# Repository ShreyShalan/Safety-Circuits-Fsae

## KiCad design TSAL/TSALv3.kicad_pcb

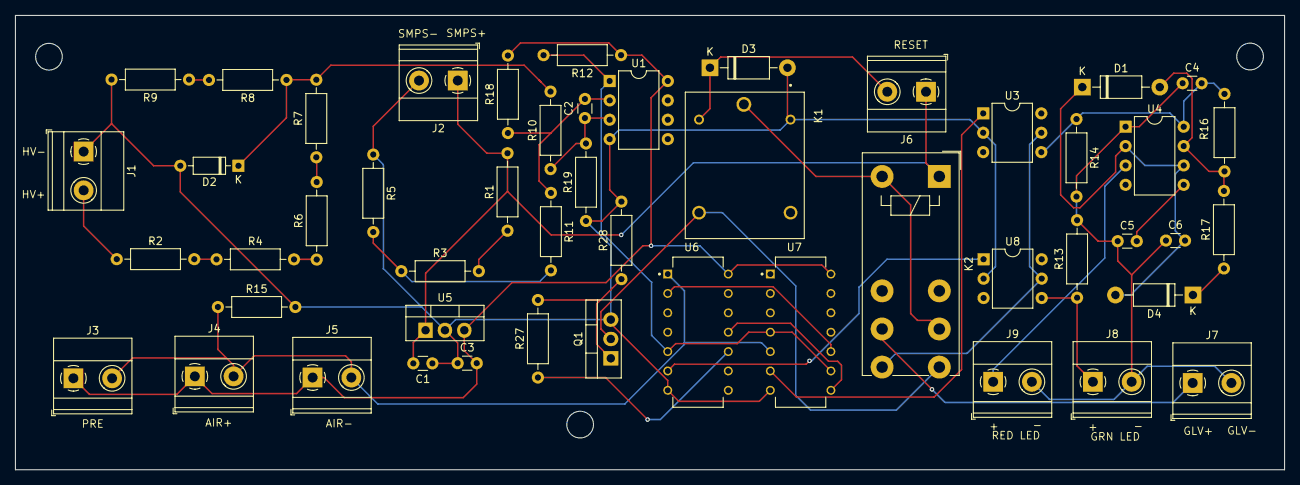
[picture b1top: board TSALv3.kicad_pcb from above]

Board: 2 copper layers, 166.4 x 59.6 mm, 50 parts (0 on the bottom side), 34 nets.

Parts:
C1: 0.33u; C_Disc_D3.0mm_W1.6mm_P2.50mm
C2: 10n; C_Disc_D3.0mm_W1.6mm_P2.50mm
C3: 0.1u; C_Disc_D3.0mm_W1.6mm_P2.50mm
C4, C5: 100n; C_Disc_D3.0mm_W1.6mm_P2.50mm
C6: 1u; C_Disc_D3.0mm_W1.6mm_P2.50mm
D1, D3, D4: 1N4002; D_DO-41_SOD81_P10.16mm_Horizontal
D2: 12V; D_DO-35_SOD27_P7.62mm_Horizontal
J1, J2, J3, J4, J5, J6, J7, J8, J9: Screw_Terminal_01x02; TerminalBlock_Phoenix_MKDS-1,5-2-5.08_1x02_P5.08mm_Horizont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
K1: SRD-12VDC-SL-C; RELAY_SRD-12VDC-SL-C
K2: FINDER-40.52; Relay_DPDT_Finder_40.52
Q1: IRF540N; TO-220-3_Vertical
R1, R13, R14, R15, R28: 10k; R_Axial_DIN0207_L6.3mm_D2.5mm_P10.16mm_Horizontal
R2, R4, R6: 47k; R_Axial_DIN0207_L6.3mm_D2.5mm_P10.16mm_Horizontal
R3, R8, R9, R12, R18, R19: 1k; R_Axial_DIN0207_L6.3mm_D2.5mm_P10.16mm_Horizontal
R5: 1K; R_Axial_DIN0207_L6.3mm_D2.5mm_P10.16mm_Horizontal
R7: 249k; R_Axial_DIN0207_L6.3mm_D2.5mm_P10.16mm_Horizontal
R10, R11, R27: 100; R_Axial_DIN0207_L6.3mm_D2.5mm_P10.16mm_Horizontal
R16, R17: 180k; R_Axial_DIN0207_L6.3mm_D2.5mm_P10.16mm_Horizontal
U1: LM393; DIP-8_W7.62mm
U3, U8: 4N35; DIP-6_W7.62mm
U4: NE555P; DIP-8_W7.62mm
U5: L7805; TO-220-3_Vertical
U6: SN74LS04N; DIP794W45P254L1969H508Q14
U7: SN74LS08N; DIP794W45P254L1969H508Q14

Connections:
+5V: C3.2, J3.1, J4.1, J5.1, R12.1, R18.2, U1.8 (V+), U5.3 (OUT), U6.14 (VCC), U7.14 (VCC)
+12V: C1.2, J2.1, J6.1, K2.A1, R1.2, U5.1 (IN)
/+HV: J1.2, R2.1
/GRN+: J8.1, R13.1, U8.4
/RED+: J9.1, U4.3 (Q)
/Vin: D2.1 (K), R7.2, R8.1, R10.2
/Vref: R3.1, R5.2, R11.2
AIR State: J3.2, J4.2, J5.2, R15.1, U6.1 (1A), U7.5 (2B)
AUX Open: U6.2 (1Y), U7.10 (3B)
GLV supply: K2.24, U3.5, U8.5
GLV+: J7.1, K2.21
GLV-: C4.1, C5.1, C6.1, J7.2, J8.2, J9.2, R13.2, R14.2, U4.1 (GND)
GND: C1.1, C3.1, D2.2 (A), D3.2 (A), J1.1, J2.2, K1.COIL1, Q1.3 (S), R5.1, R9.2, R15.2, R19.1, R28.2, U1.4 (V-), U3.2, U5.2 (GND), U6.7 (GND), U7.7 (GND), U8.2
unnamed: D1.2 (A), R16.1, R17.2, U4.7 (DIS)
unnamed: C6.2, D1.1 (K), D4.2 (A), U4.2 (TR), U4.6 (THR)
unnamed: D4.1 (K), R17.1
unnamed: K1.COM, K2.11, K2.A2
unnamed: K1.NO, K2.14, Q1.2 (D)
unnamed: Q1.1 (G), R27.2, R28.1
unnamed: R1.1, R3.2
unnamed: R2.2, R4.1
unnamed: R4.2, R6.1
unnamed: R6.2, R7.1
unnamed: R8.2, R9.1
unnamed: C2.1, R10.1, R19.2, U1.3 (+)
unnamed: C2.2, R11.1, R18.1, U1.2 (-)
unnamed: C5.2, U4.5 (CV)
unnamed: C4.2, R14.1, R16.2, U3.4, U4.8 (VCC)
RED ON: U3.1, U7.6 (2Y)
TS Status: R12.2, U1.1, U6.5 (3A), U7.4 (2A), U7.9 (3A)
TS' Status: U6.6 (3Y), U8.1
TSAL Error: U6.11 (5A), U7.8 (3Y)
TSAL Error': R27.1, U6.10 (5Y)
reset: D3.1 (K), J6.2, K1.COIL2

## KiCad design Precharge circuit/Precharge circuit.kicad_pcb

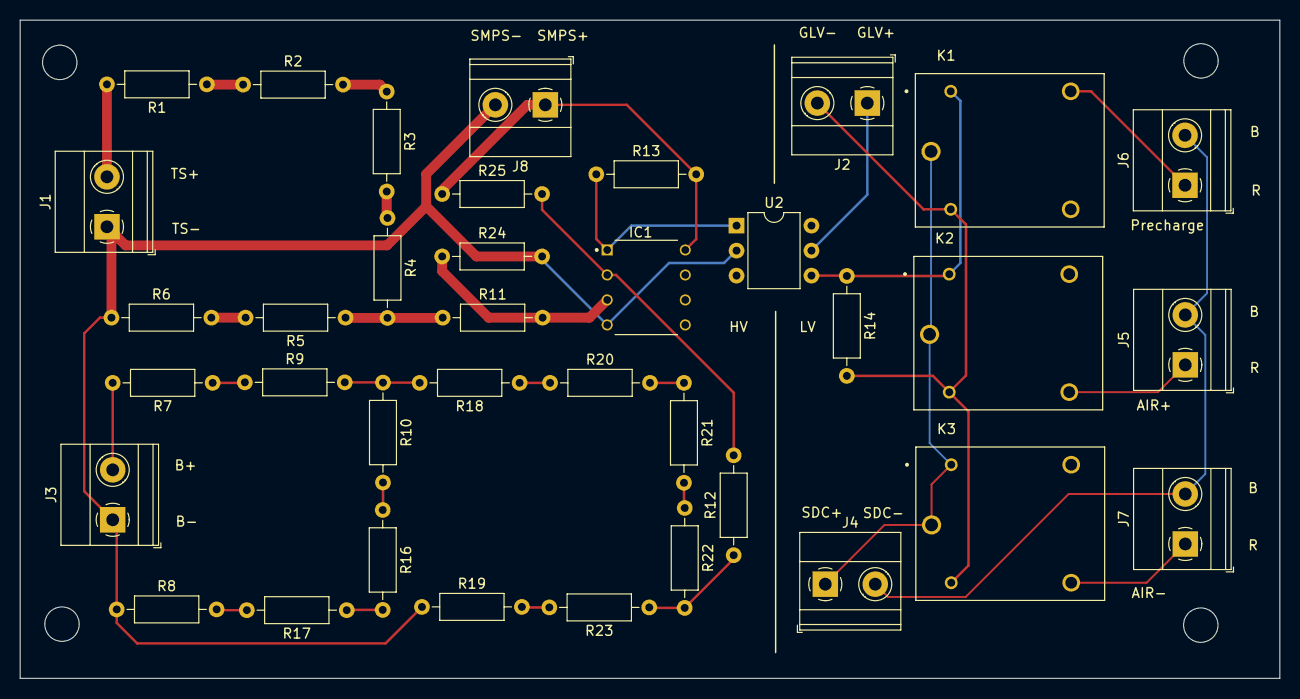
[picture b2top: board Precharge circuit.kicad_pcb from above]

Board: 2 copper layers, 128.1 x 66.9 mm, 37 parts (0 on the bottom side), 30 nets.

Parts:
IC1: LM393AN; DIP794W45P254L959H508Q8
J1, J3: Conn_01x02_Socket; TerminalBlock_Phoenix_MKDS-1,5-2-5.08_1x02_P5.08mm_Horizont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
J2, J4, J5, J6, J7, J8: Screw_Terminal_01x02; TerminalBlock_Phoenix_MKDS-1,5-2-5.08_1x02_P5.08mm_Horizont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
K1, K2, K3: SRD-12VDC-SL-C; RELAY_SRD-12VDC-SL-C
R1, R2, R10, R16, R18, R20: 120k; R_Axial_DIN0207_L6.3mm_D2.5mm_P10.16mm_Horizontal
R3, R17, R21: 82k; R_Axial_DIN0207_L6.3mm_D2.5mm_P10.16mm_Horizontal
R4, R5, R6, R19, R22, R23: 1k; R_Axial_DIN0207_L6.3mm_D2.5mm_P10.16mm_Horizontal
R7, R9, R13, R14, R24, R25: 10k; R_Axial_DIN0207_L6.3mm_D2.5mm_P10.16mm_Horizontal
R8: 64k; R_Axial_DIN0207_L6.3mm_D2.5mm_P10.16mm_Horizontal
R11, R12: 100; R_Axial_DIN0207_L6.3mm_D2.5mm_P10.16mm_Horizontal
U2: 4N35; DIP-6_W7.62mm

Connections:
+12V: IC1.8 (VCC), J8.1, R13.2, R25.1
AIR+: J5.1, K2.NO
AIR-: J7.1, K3.NO
GND: IC1.4 (GND), J1.1, J3.1, J8.2, R6.1, R8.1, R19.1, R24.2, U2.2
GND1: J2.2, K1.COIL2, K2.COIL2, K3.COIL2, R14.2
unnamed: IC1.3 (1IN+), R11.2, R24.1
unnamed: IC1.2 (1IN-), R12.2, R25.2
unnamed: IC1.1 (1OUT), R13.1, U2.1
unnamed: J1.2, R1.2
unnamed: J3.2, R7.2
unnamed: R1.1, R2.1
unnamed: R2.2, R3.1
unnamed: R3.2, R4.1
unnamed: R5.2, R6.2
unnamed: R7.1, R9.1
unnamed: R9.2, R10.1, R18.2
unnamed: R10.2, R16.1
unnamed: R4.2, R5.1, R11.1
unnamed: R12.1, R22.2, R23.1
unnamed: R16.2, R17.1
unnamed: R8.2, R17.2
unnamed: R18.1, R20.1
unnamed: R19.2, R23.2
unnamed: R20.2, R21.1
unnamed: R21.2, R22.1
SDC+: J4.1, K1.COM, K2.COM, K3.COIL1, K3.COM
SDC-: J4.2, J5.2, J6.2, J7.2
VCC: J2.1, U2.5
precharge: J6.1, K1.NC
rpower: K1.COIL1, K2.COIL1, R14.1, U2.4

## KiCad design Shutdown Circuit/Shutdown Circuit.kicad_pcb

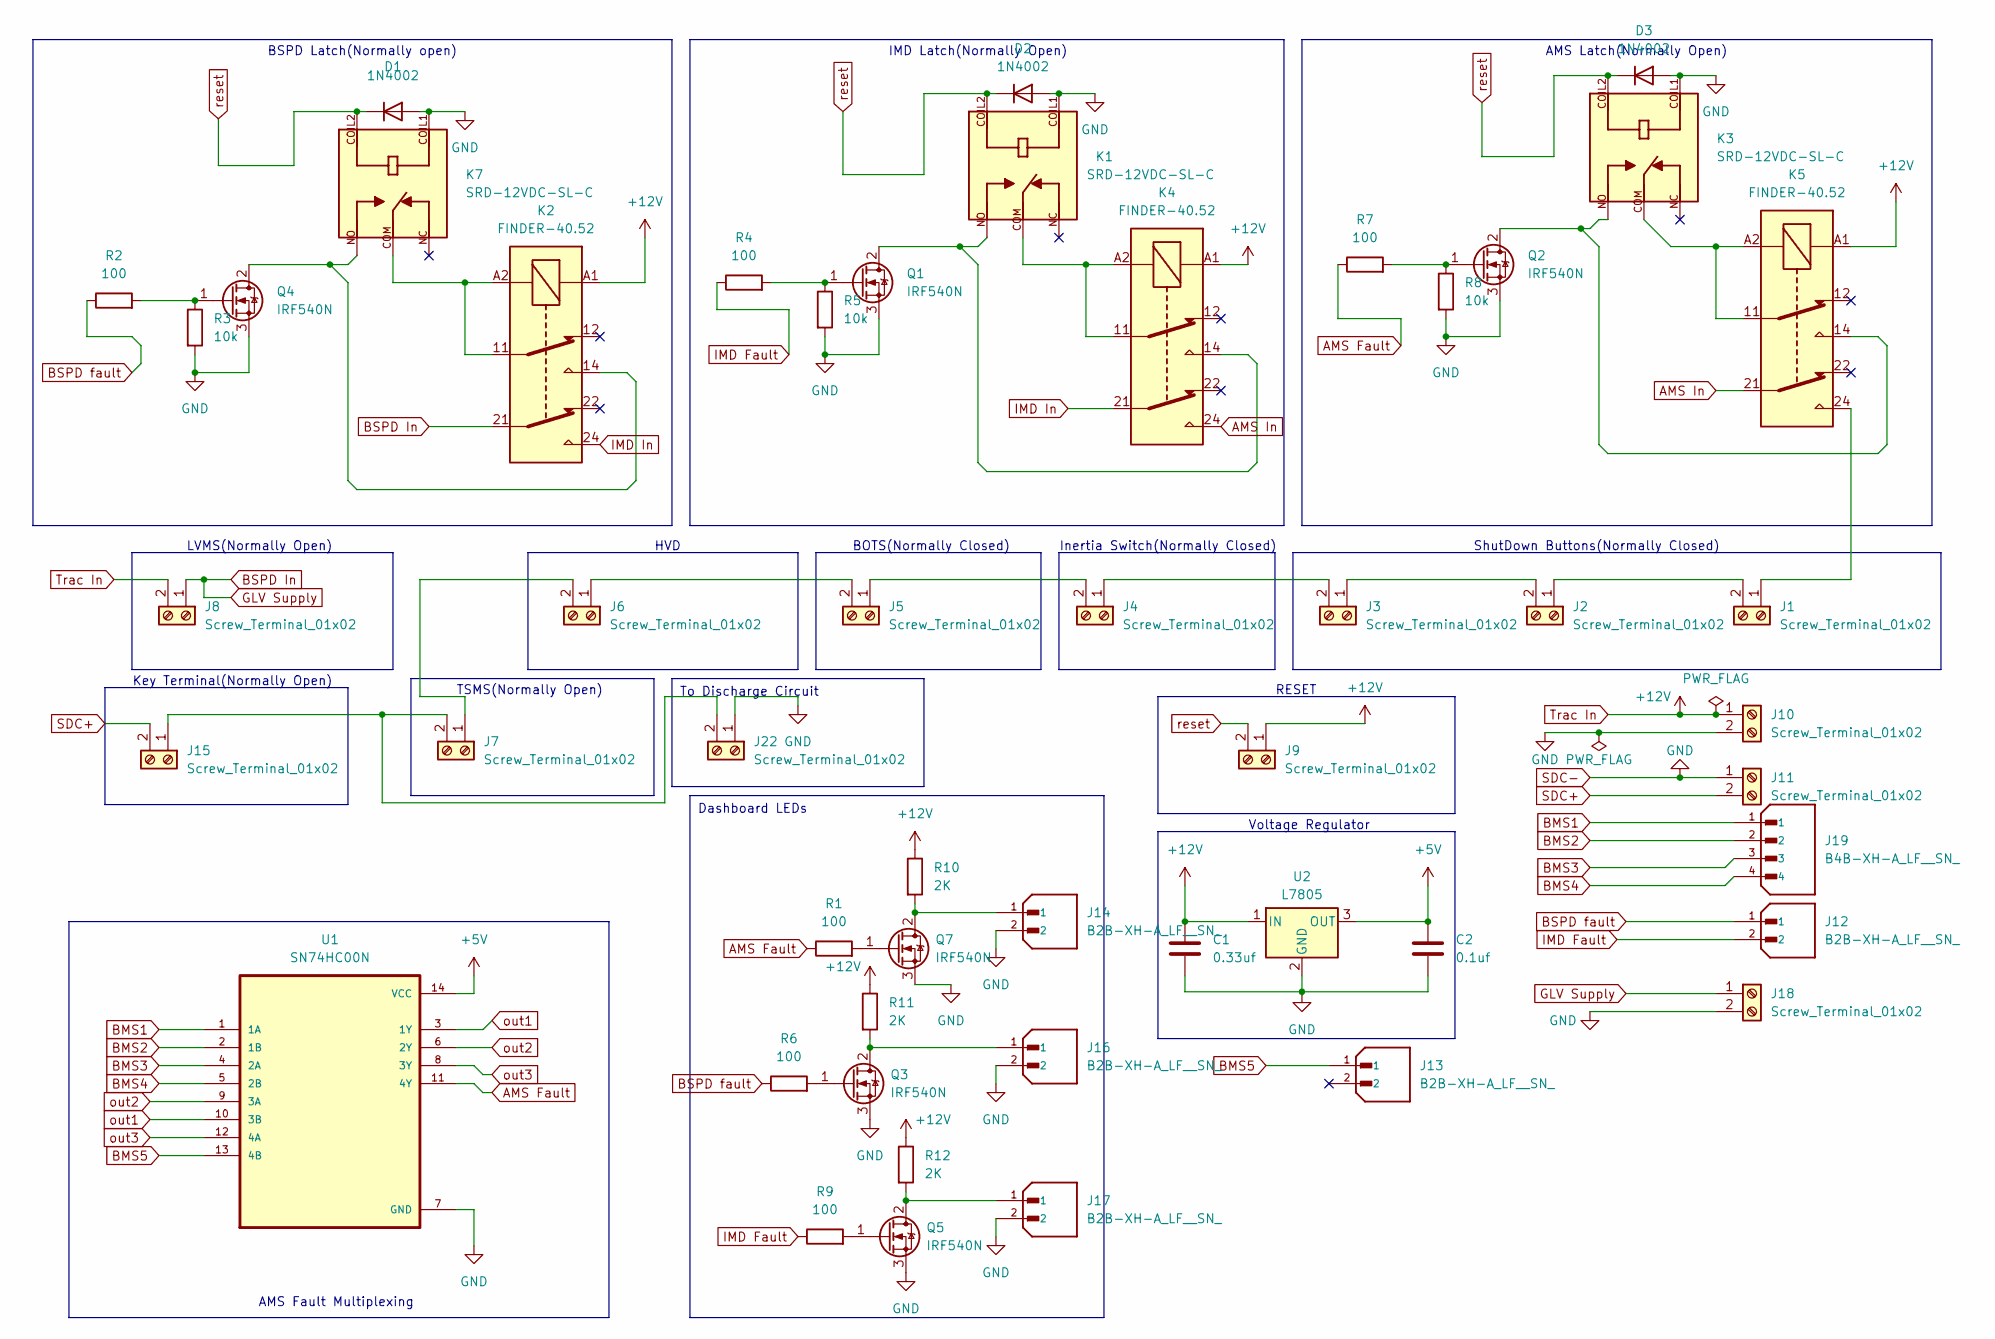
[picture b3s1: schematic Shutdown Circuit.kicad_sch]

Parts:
C1: 0.33uf; C_Disc_D5.0mm_W2.5mm_P5.00mm
C2: 0.1uf; C_Disc_D5.0mm_W2.5mm_P5.00mm
D1, D2, D3: 1N4002; D_DO-41_SOD81_P10.16mm_Horizontal
J1, J2, J3, J4, J5, J6, J7, J8, J9, J10, J11, J15, J18, J22: Screw_Terminal_01x02; TerminalBlock_Phoenix_MKDS-1,5-2-5.08_1x02_P5.08mm_Horizont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
J12, J13, J14, J16, J17: B2B-XH-A_LF__SN_; JST_B2B-XH-A_LF__SN_; PARTREV N/A
J19: B4B-XH-A_LF__SN_; JST_B4B-XH-A_LF__SN_; PARTREV 7/4/21
K1, K3, K7: SRD-12VDC-SL-C; RELAY_SRD-12VDC-SL-C; PARTREV 1.0
K2, K4, K5: FINDER-40.52; Relay_DPDT_Finder_40.52
Q1, Q2, Q3, Q4, Q5, Q7: IRF540N; TO-220-3_Vertical
R1, R2, R4, R6, R7, R9: 100; R_Axial_DIN0207_L6.3mm_D2.5mm_P10.16mm_Horizontal
R3, R5, R8: 10k; R_Axial_DIN0207_L6.3mm_D2.5mm_P10.16mm_Horizontal
R10, R11, R12: 2K; R_Axial_DIN0207_L6.3mm_D2.5mm_P10.16mm_Horizontal
U1: SN74HC00N; DIP794W45P254L1969H508Q14
U2: L7805; TO-220-3_Vertical

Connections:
+5V: C2.1, U1.14 (VCC), U2.3 (OUT)
AMS Fault: R1.1, R7.1, U1.11 (4Y)
AMS In: K4.24, K5.21
BMS1: J19.1, U1.1 (1A)
BMS2: J19.2, U1.2 (1B)
BMS3: J19.3, U1.4 (2A)
BMS4: J19.4, U1.5 (2B)
BMS5: J13.1, U1.13 (4B)
BSPD In: J8.1, J18.1, K2.21
BSPD fault: J12.1, R2.1, R6.1
IMD Fault: J12.2, R4.1, R9.1
IMD In: K2.24, K4.21
unnamed: J1.1, K5.24
unnamed: J1.2, J2.1
unnamed: J2.2, J3.1
unnamed: J3.2, J4.1
unnamed: J4.2, J5.1
unnamed: J5.2, J6.1
unnamed: J6.2, J7.1
unnamed: J7.2, J15.1, J22.2
unnamed: K1.COM, K4.11, K4.A2
unnamed: K2.11, K2.A2, K7.COM
unnamed: K3.COM, K5.11, K5.A2
unnamed: K1.NO, K4.14, Q1.2 (D)
unnamed: Q1.1 (G), R4.2, R5.1
unnamed: K3.NO, K5.14, Q2.2 (D)
unnamed: Q2.1 (G), R7.2, R8.1
unnamed: J16.1, Q3.2 (D), R11.2
unnamed: Q3.1 (G), R6.2
unnamed: K2.14, K7.NO, Q4.2 (D)
unnamed: Q4.1 (G), R2.2, R3.1
unnamed: J17.1, Q5.2 (D), R12.2
unnamed: Q5.1 (G), R9.2
unnamed: J14.1, Q7.2 (D), R10.2
unnamed: Q7.1 (G), R1.2
SDC+: J11.2, J15.2
SDC-: C1.2, C2.2, D1.2 (A), D2.2 (A), D3.2 (A), J10.2, J11.1, J14.2, J16.2, J17.2, J18.2, J22.1, K1.COIL1, K3.COIL1, K7.COIL1, Q1.3 (S), Q2.3 (S), Q3.3 (S), Q4.3 (S), Q5.3 (S), Q7.3 (S), R3.2, R5.2, R8.2, U1.7 (GND), U2.2 (GND)
Trac In: C1.1, J8.2, J9.1, J10.1, K2.A1, K4.A1, K5.A1, R10.1, R11.1, R12.1, U2.1 (IN)
out1: U1.3 (1Y), U1.10 (3B)
out2: U1.6 (2Y), U1.9 (3A)
out3: U1.8 (3Y), U1.12 (4A)
reset: D1.1 (K), D2.1 (K), D3.1 (K), J9.2, K1.COIL2, K3.COIL2, K7.COIL2

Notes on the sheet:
To Discharge Circuit
Dashboard LEDs
AMS Latch(Normally Open)
LVMS(Normally Open)
BOTS(Normally Closed)
HVD
TSMS(Normally Open)
AMS Fault Multiplexing
IMD Latch(Normally Open)
BSPD Latch(Normally open)
RESET
ShutDown Buttons(Normally Closed)
Inertia Switch(Normally Closed)
Voltage Regulator
Key Terminal(Normally Open)

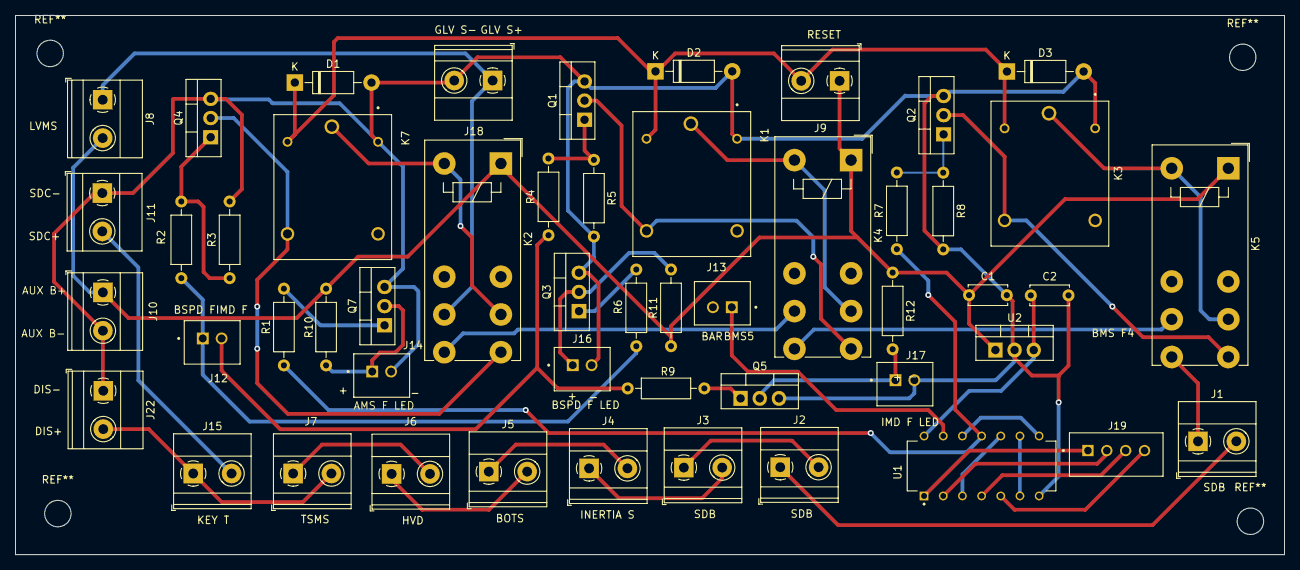
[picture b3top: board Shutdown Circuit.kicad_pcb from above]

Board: 2 copper layers, 168.1 x 71.4 mm, 51 parts (0 on the bottom side), 42 nets.

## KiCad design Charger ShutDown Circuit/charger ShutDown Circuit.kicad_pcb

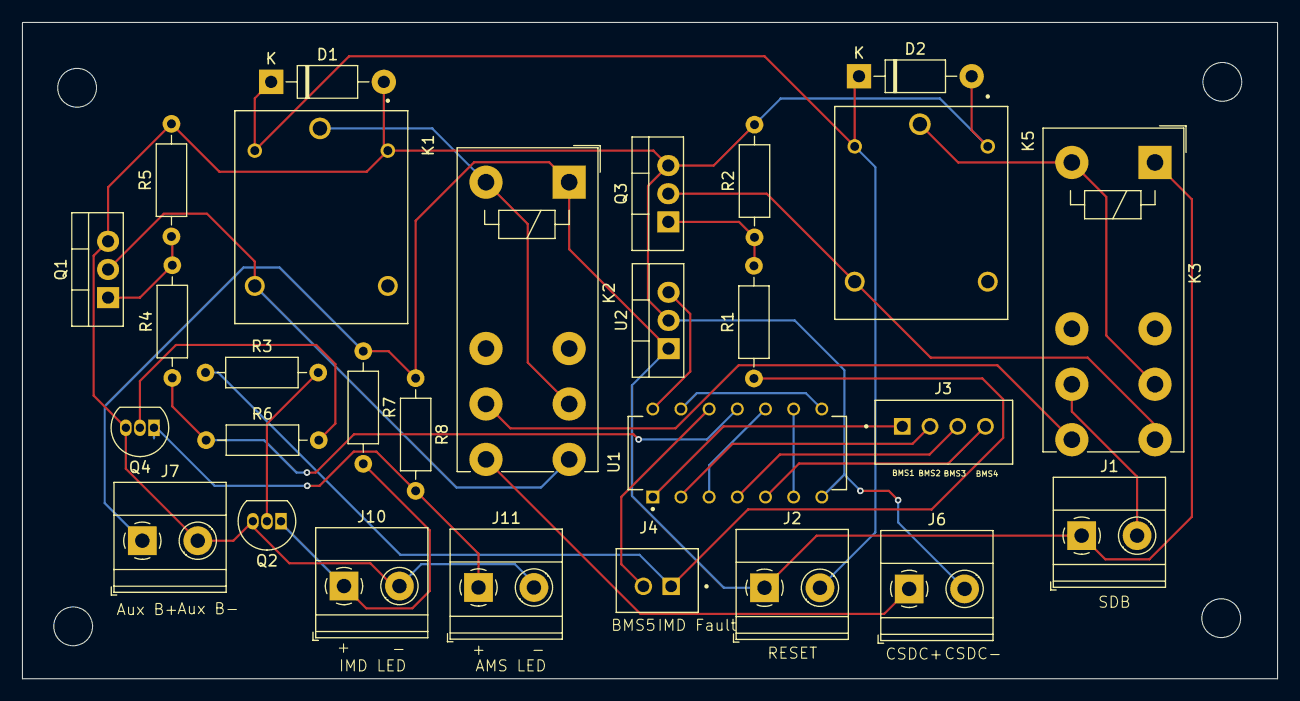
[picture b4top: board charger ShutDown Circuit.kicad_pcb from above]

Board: 2 copper layers, 113.2 x 59.2 mm, 28 parts (0 on the bottom side), 27 nets.

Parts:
D1, D2: 1N4007; D_DO-41_SOD81_P10.16mm_Horizontal
J1, J2, J6, J7, J10, J11: Screw_Terminal_01x02; TerminalBlock_Phoenix_MKDS-1,5-2_1x02_P5.00mm_Horizontal
J3: B4B-XH-A_LF__SN_; JST_B4B-XH-A_LF__SN_
J4: B2B-XH-A_LF__SN_; JST_B2B-XH-A_LF__SN_
K1, K5: SRD-12VDC-SL-C; RELAY_SRD-12VDC-SL-C
K2, K3: FINDER-40.52; Relay_DPDT_Finder_40.52
Q1, Q3: IRF540N; TO-220-3_Vertical
Q2, Q4: BC547; TO-92_Inline
R1, R3, R4, R6, R7, R8: 100; R_Axial_DIN0207_L6.3mm_D2.5mm_P10.16mm_Horizontal
R2, R5: 10k; R_Axial_DIN0207_L6.3mm_D2.5mm_P10.16mm_Horizontal
U1: SN74LS32N; DIP794W45P254L1969H508Q14
U2: L7805; TO-220-3_Vertical

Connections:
+5V: U1.14 (VCC), U2.3 (OUT)
AMS Fault: R4.1, R6.1, U1.11 (4Y)
AMS In: K2.21, K3.24
Aux Battery in: J1.1, J2.1, J7.1, K2.A1, K3.A1, R7.1, R8.1, U2.1 (IN)
BMS1: J3.1, U1.1 (1A)
BMS2: J3.2, U1.2 (1B)
BMS3: J3.3, U1.4 (2A)
BMS4: J3.4, U1.5 (2B)
BMS5: J4.2, U1.12 (4A)
CSDC+: J6.1, K2.24
CSDC-: D1.2 (A), D2.2 (A), J6.2, J7.2, J10.2, J11.2, K1.COIL1, K5.COIL1, Q1.3 (S), Q2.3 (E), Q3.3 (S), Q4.3 (E), R2.2, R5.2, U1.7 (GND), U2.2 (GND)
IMD Fault: J4.1, R1.1, R3.1
IMD In: J1.2, K3.21
unnamed: J10.1, Q2.1 (C), R7.2
unnamed: J11.1, Q4.1 (C), R8.2
unnamed: K1.COM, K2.11, K2.A2
unnamed: K3.11, K3.A2, K5.COM
unnamed: K1.NO, K2.14, Q1.2 (D)
unnamed: Q1.1 (G), R4.2, R5.1
unnamed: Q2.2 (B), R3.2
unnamed: K3.14, K5.NO, Q3.2 (D)
unnamed: Q3.1 (G), R1.2, R2.1
unnamed: Q4.2 (B), R6.2
out1: U1.3 (1Y), U1.10 (3B)
out2: U1.6 (2Y), U1.9 (3A)
out3: U1.8 (3Y), U1.13 (4B)
reset: D1.1 (K), D2.1 (K), J2.2, K1.COIL2, K5.COIL2

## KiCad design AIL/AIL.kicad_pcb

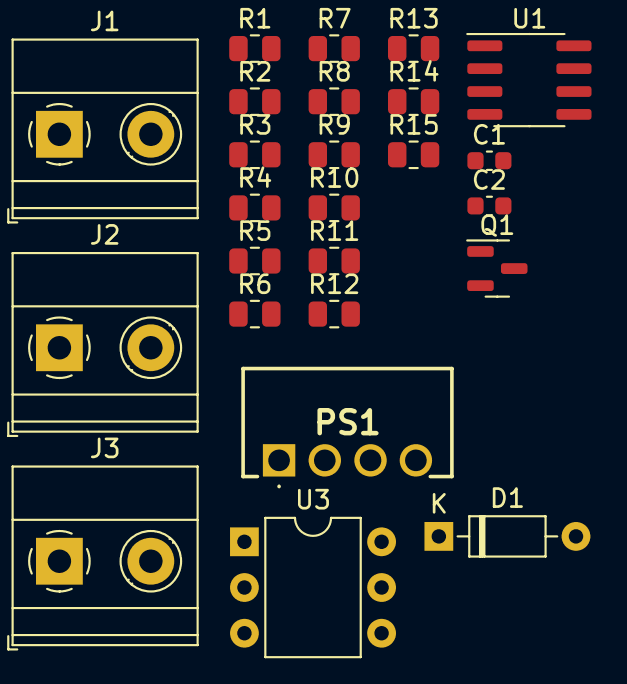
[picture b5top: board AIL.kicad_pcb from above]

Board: 2 copper layers, 25 parts (0 on the bottom side), 19 nets, no tracks yet.

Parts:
C1: 10n; C_0603_1608Metric
C2: 100n; C_0603_1608Metric
D1: 12V; D_DO-35_SOD27_P7.62mm_Horizontal
J1, J2, J3: Screw_Terminal_01x02; TerminalBlock_Phoenix_MKDS-1,5-2-5.08_1x02_P5.08mm_Horizont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
PS1: IEB0112S12
Q1: 2N7002; SOT-23
R1, R4: 47k; R_0805_2012Metric
R2, R5, R6, R7: 12k; R_0805_2012Metric
R3, R8: 1k; R_0805_2012Metric
R9, R14: 10k; R_0805_2012Metric
R10: 3.3k; R_0805_2012Metric
R11, R12: 100; R_0805_2012Metric
R13: 1M; R_0805_2012Metric
R15: 22k; R_0805_2012Metric
U1: LM311; SOIC-8_3.9x4.9mm_P1.27mm
U3: 4N35; DIP-6_W7.62mm

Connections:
+12V: PS1.4 (+VOUT), R2.2, U1.8 (V+), U3.1
AIL_LED: J3.1, Q1.3 (D), R15.2
GND: C2.1, C2.2, D1.2 (A), J1.1, PS1.3 (-VOUT), R3.1, R10.2, U1.1 (GND), U1.4 (V-)
GND1: J2.2, J3.2, PS1.1 (-VIN), Q1.2 (S), R14.2
unnamed: D1.1 (K), R7.2, R8.1, R11.1
unnamed: J1.2, R1.2
unnamed: Q1.1 (G), R14.1, U3.4
unnamed: R1.1, R4.1
unnamed: R2.1, R5.2
unnamed: R3.2, R8.2
unnamed: R4.2, R6.1
unnamed: R5.1, R9.2
unnamed: R6.2, R7.1
unnamed: R9.1, R10.1, R12.1
unnamed: R13.2, U1.7, U3.2
unnamed: C1.1, R11.2, R13.1, U1.2 (+)
unnamed: C1.2, R12.2, U1.3 (-)
unnamed: U1.5 (BAL), U1.6 (STRB)
VCC: J2.1, PS1.2 (+VIN), R15.1, U3.5

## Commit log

2024-02-18 Final commit
